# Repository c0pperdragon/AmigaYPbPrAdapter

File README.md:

# Amiga YPbPr Adapter

To get the best possible image quality from a vintage Amiga (specifically Amiga 500) home computer.

The Amiga basically supports RGB output natively, but this standard is not suitable to directly
feed into a modern mid-range TV. The way to go with current TVs is component video (a.k.a YPbPr) that
has basically the same quality as RGB but uses a different way to encode everything.

As a matter of fact, the Y of YPbPr is just the (monochrome) luma signal together with sync, which is 
identical to the signal many Amiga computers (the 1000, 500, 2000 and maybe others as well) already provide 
on their composite output port. 
So it is only necessary to create the suitable Pb and Pr signals to get full-blown YPbPr.

The adapter is intended to plug into the RGB video connector to produce the two missing signals.
Unluckily the RGB connector of the Amiga requires a female 23-pin SUB-D plug, and these connectors
are no longer in production. A 25-pin connector can be trimmed down to somehow fit, but this
requires quite some manual work and mass-production is out of the question. 

Nevertheless, I make everything open source in case someone else wants to build it. It is especially designed
for home-etching so it uses only a single-sided board with some jumper wires on the other side. 
The only non-trivial components are the 3 op-amp packages (with 2 op-amps each). These must be some standard
high-speed parts in SOIC-8 packages. Rail-to-rail operation with 5 volt supply is preferable, but it should
also work with other parts as well.

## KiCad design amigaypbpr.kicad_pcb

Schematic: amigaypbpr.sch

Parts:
C1: 10uF; C_0805_2012Metric_Pad1.15x1.40mm_HandSolder
C2, C4, C5: 100nF; C_0805_2012Metric_Pad1.15x1.40mm_HandSolder
J1: DB25_Female; DSUB-25_Female_Horizontal_P2.77x2.84mm_EdgePinOffset9.40mm
J2: PB; RCA_JACK
J3: PR; RCA_JACK
R1, R6, R8: 4k7; R_0805_2012Metric_Pad1.15x1.40mm_HandSolder
R2: 2k2; R_0805_2012Metric_Pad1.15x1.40mm_HandSolder
R3, R7, R11, R12, R13, R14: 1k; R_0805_2012Metric_Pad1.15x1.40mm_HandSolder
R4, R10: 10k; R_0805_2012Metric_Pad1.15x1.40mm_HandSolder
R5, R9: 1k5; R_0805_2012Metric_Pad1.15x1.40mm_HandSolder
R15, R16: 75; R_0805_2012Metric_Pad1.15x1.40mm_HandSolder
U1, U2, U3: OPA2356xxD; SOIC-8_3.9x4.9mm_P1.27mm

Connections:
+5V: C1.1, C2.1, C4.1, C5.1, J1.25, R1.1, U1.8 (V+), U2.8 (V+), U3.8 (V+)
/BLUE: R3.2, R4.2, R10.2, U1.1, U1.2 (-)
/GREEN: R5.2, R9.2, U2.1, U2.2 (-)
/RED: R6.2, R7.2, R8.2, U3.1, U3.2 (-)
/ZERO: R11.1, R12.1, U2.6 (-), U2.7
GND: C1.2, C2.2, C4.2, C5.2, J1.18, J1.19, J1.20, J2.2, J3.2, R2.2, U1.4 (V-), U2.4 (V-), U3.4 (V-)
unnamed: J1.4, U3.3 (+)
unnamed: J1.5, U2.3 (+)
unnamed: J1.6, U1.3 (+)
unnamed: J2.1, R15.1
unnamed: J3.1, R16.1
unnamed: R1.2, R2.1, U2.5 (+)
unnamed: R8.1, R9.1, R10.1, R14.2, U3.6 (-)
unnamed: R3.1, R11.2, U1.5 (+)
unnamed: R7.1, R12.2, U3.5 (+)
unnamed: R13.1, R15.2, U1.7
unnamed: R4.1, R5.1, R6.1, R13.2, U1.6 (-)
unnamed: R14.1, R16.2, U3.7

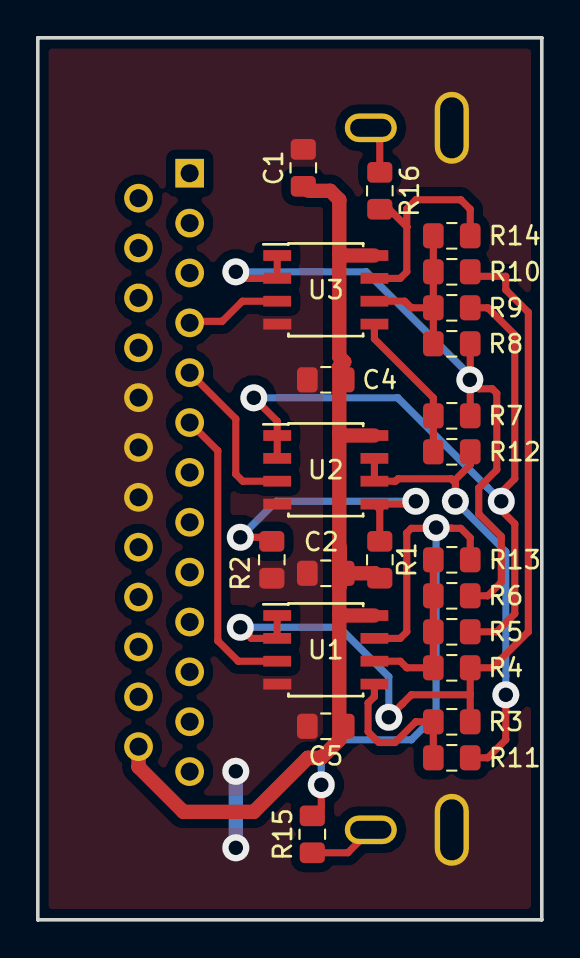
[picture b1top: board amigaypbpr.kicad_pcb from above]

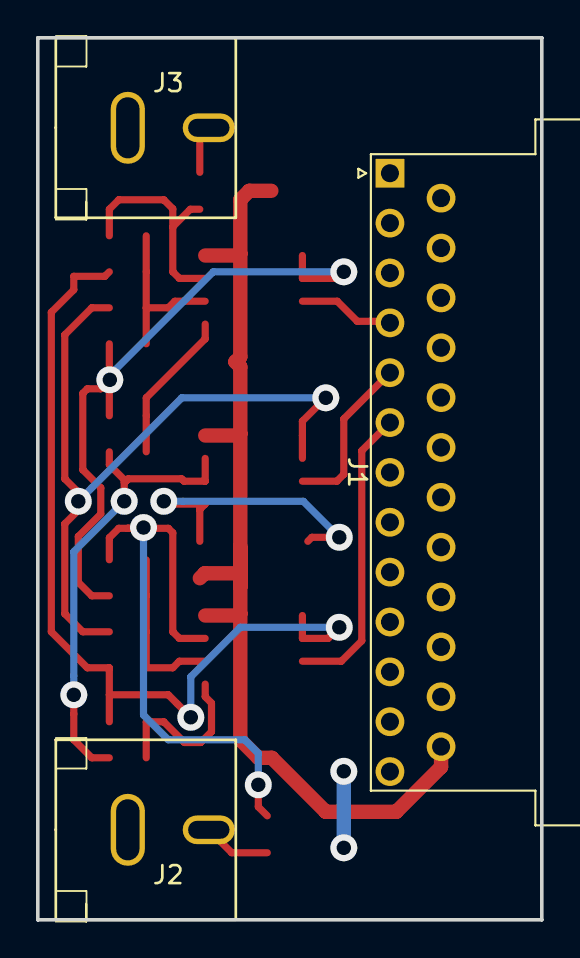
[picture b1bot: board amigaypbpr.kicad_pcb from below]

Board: 2 copper layers, 28.0 x 49.0 mm, 26 parts (3 on the bottom side), 18 nets.

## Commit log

2019-07-25 Board design and layout
2019-07-29 More documentation and pictures
2019-07-29 Fix docu
